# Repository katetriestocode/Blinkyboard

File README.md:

# Blinkyboard

following hackclub starter project blinky board! shaped like a flower and smells like one too ;) jk i doubt pcbs have a smell of flowers. 

this has: 10 leds, a ne555p, and a cd4017 :D

this is the final build! it was one of my first soldering experiences but it turned out great!

this is the render:

this is the pcb:

this is the schematic:

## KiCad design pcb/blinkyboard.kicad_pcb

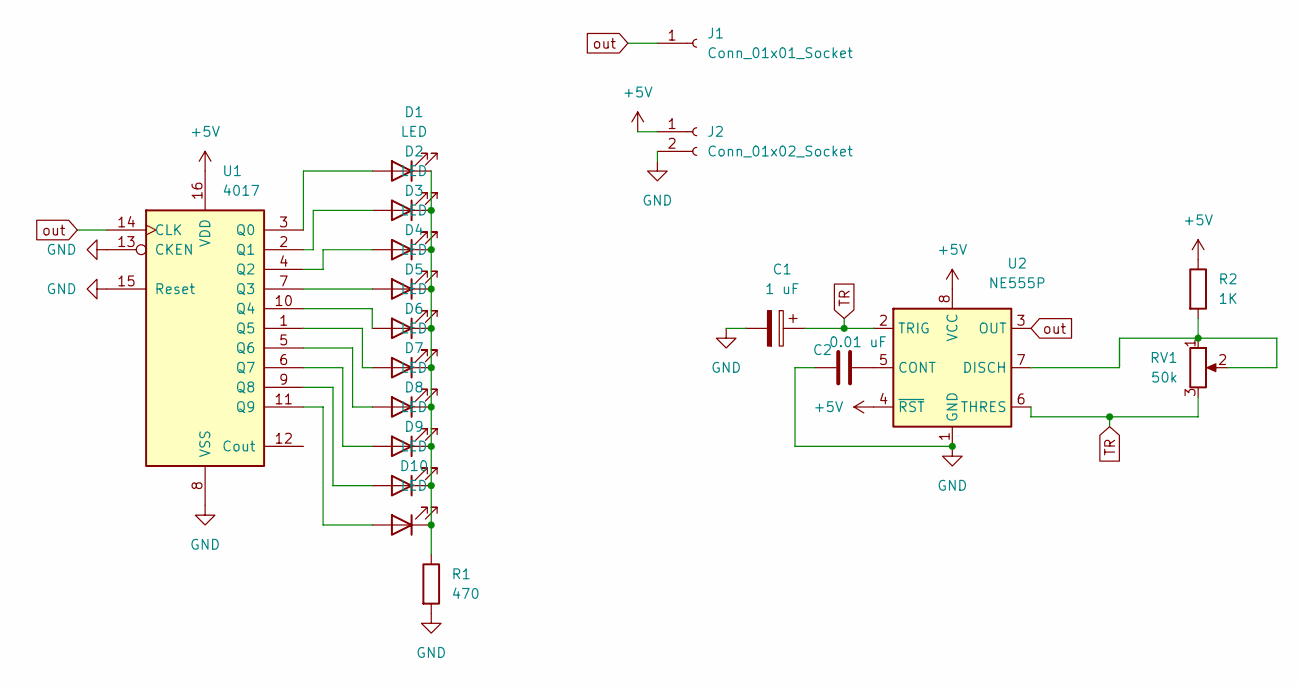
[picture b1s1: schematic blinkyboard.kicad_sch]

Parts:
C1: 1 uF; CP_Radial_D5.0mm_P2.00mm
C2: 0.01 uF; C_Disc_D7.5mm_W2.5mm_P5.00mm
D1, D2, D3, D4, D5, D6, D7, D8, D9, D10: LED; LED_D3.0mm
J1: Conn_01x01_Socket; PinHeader_1x01_P2.54mm_Vertical
J2: Conn_01x02_Socket; PinHeader_1x02_P2.54mm_Vertical
R1: 470; R_Axial_DIN0207_L6.3mm_D2.5mm_P7.62mm_Horizontal
R2: 1K; R_Axial_DIN0207_L6.3mm_D2.5mm_P7.62mm_Horizontal
RV1: 50k; Potentiometer_Vishay_T93YA_Vertical
U1: 4017; N16
U2: NE555P; DIP-8_W7.62mm

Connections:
+5V: J2.1, R2.1, U1.16 (VDD), U2.4 (~RST), U2.8 (VCC)
GND: C1.2, C2.2, J2.2, R1.2, U1.8 (VSS), U1.13 (CKEN), U1.15 (Reset), U2.1 (GND)
unnamed: D1.2 (A), U1.3 (Q0)
unnamed: D1.1 (K), D2.1 (K), D3.1 (K), D4.1 (K), D5.1 (K), D6.1 (K), D7.1 (K), D8.1 (K), D9.1 (K), D10.1 (K), R1.1
unnamed: D2.2 (A), U1.2 (Q1)
unnamed: D3.2 (A), U1.4 (Q2)
unnamed: D4.2 (A), U1.7 (Q3)
unnamed: D5.2 (A), U1.10 (Q4)
unnamed: D6.2 (A), U1.1 (Q5)
unnamed: D7.2 (A), U1.5 (Q6)
unnamed: D8.2 (A), U1.6 (Q7)
unnamed: D9.2 (A), U1.9 (Q8)
unnamed: D10.2 (A), U1.11 (Q9)
unnamed: C2.1, U2.5 (CONT)
unnamed: R2.2, RV1.1, RV1.2, U2.7 (DISCH)
TR: C1.1, RV1.3, U2.2 (TRIG), U2.6 (THRES)
out: J1.1, U1.14 (CLK), U2.3 (OUT)

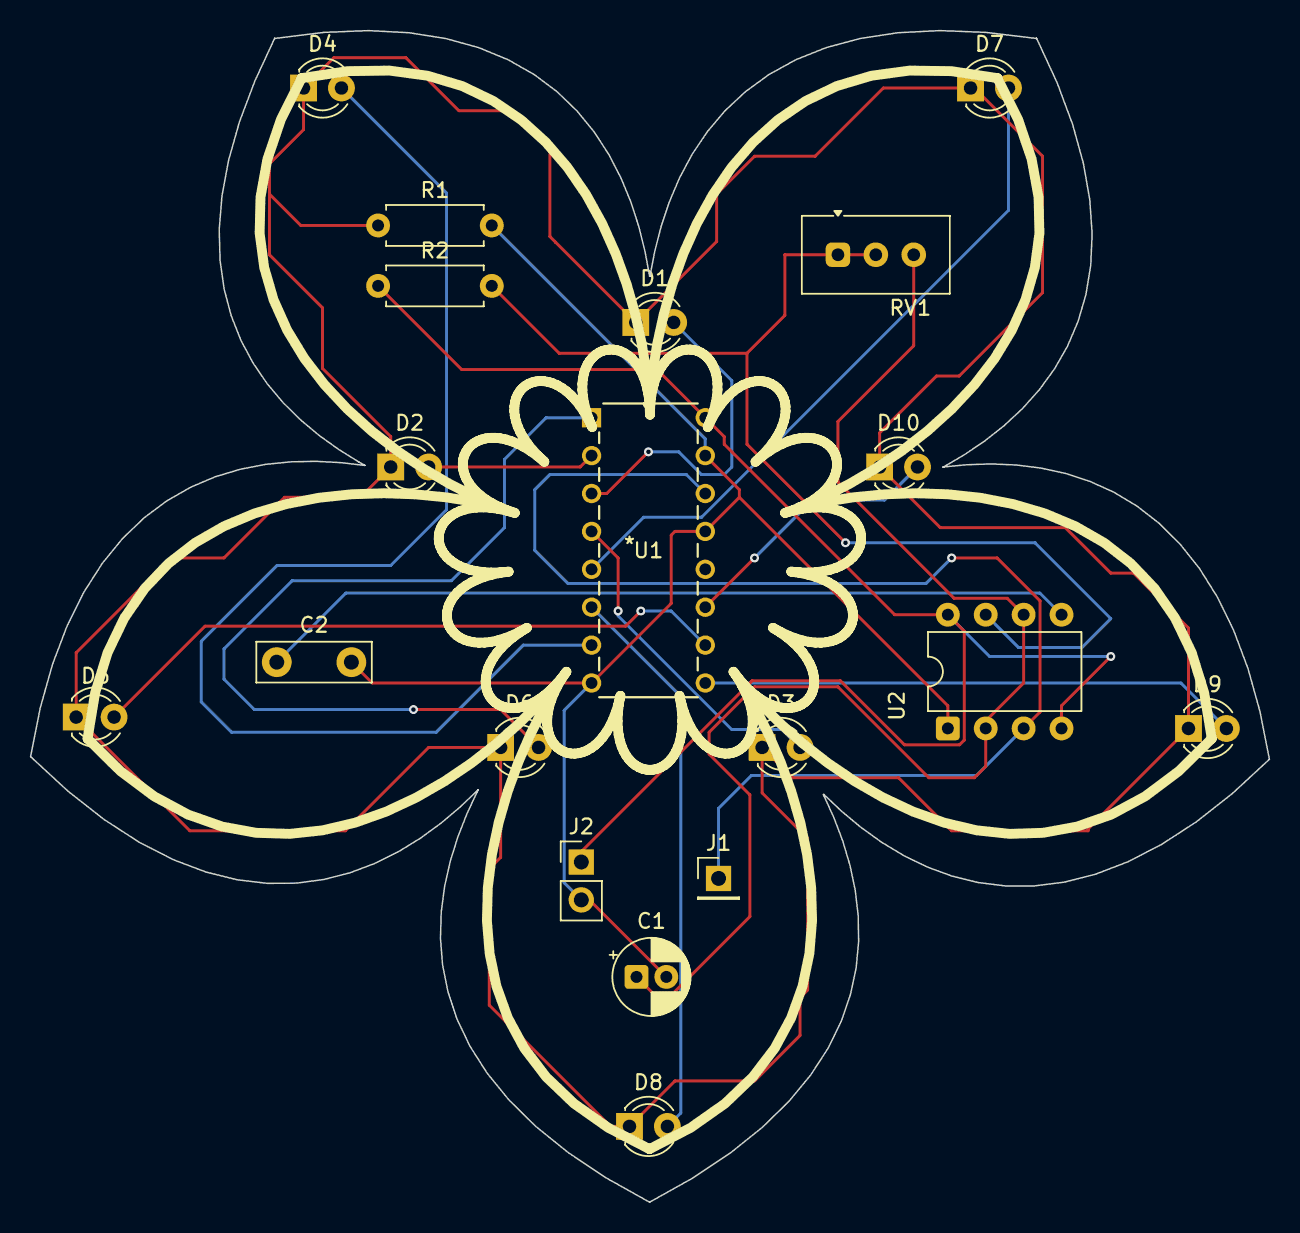
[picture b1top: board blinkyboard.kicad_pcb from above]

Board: 2 copper layers, 83.0 x 78.5 mm, 19 parts (0 on the bottom side), 17 nets.

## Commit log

2026-04-23 pcb2
2026-04-23 peep
2026-04-23 blorp
2026-04-23 zorp
2026-04-24 Update README with project journal entries
    Added journal entries and personal notes for the project.
2026-06-16 build rev
2026-06-17 photos
2026-06-17 pic2
2026-06-17 boop
2026-06-17 bing
2026-06-17 gif added
2026-06-17 new pic
